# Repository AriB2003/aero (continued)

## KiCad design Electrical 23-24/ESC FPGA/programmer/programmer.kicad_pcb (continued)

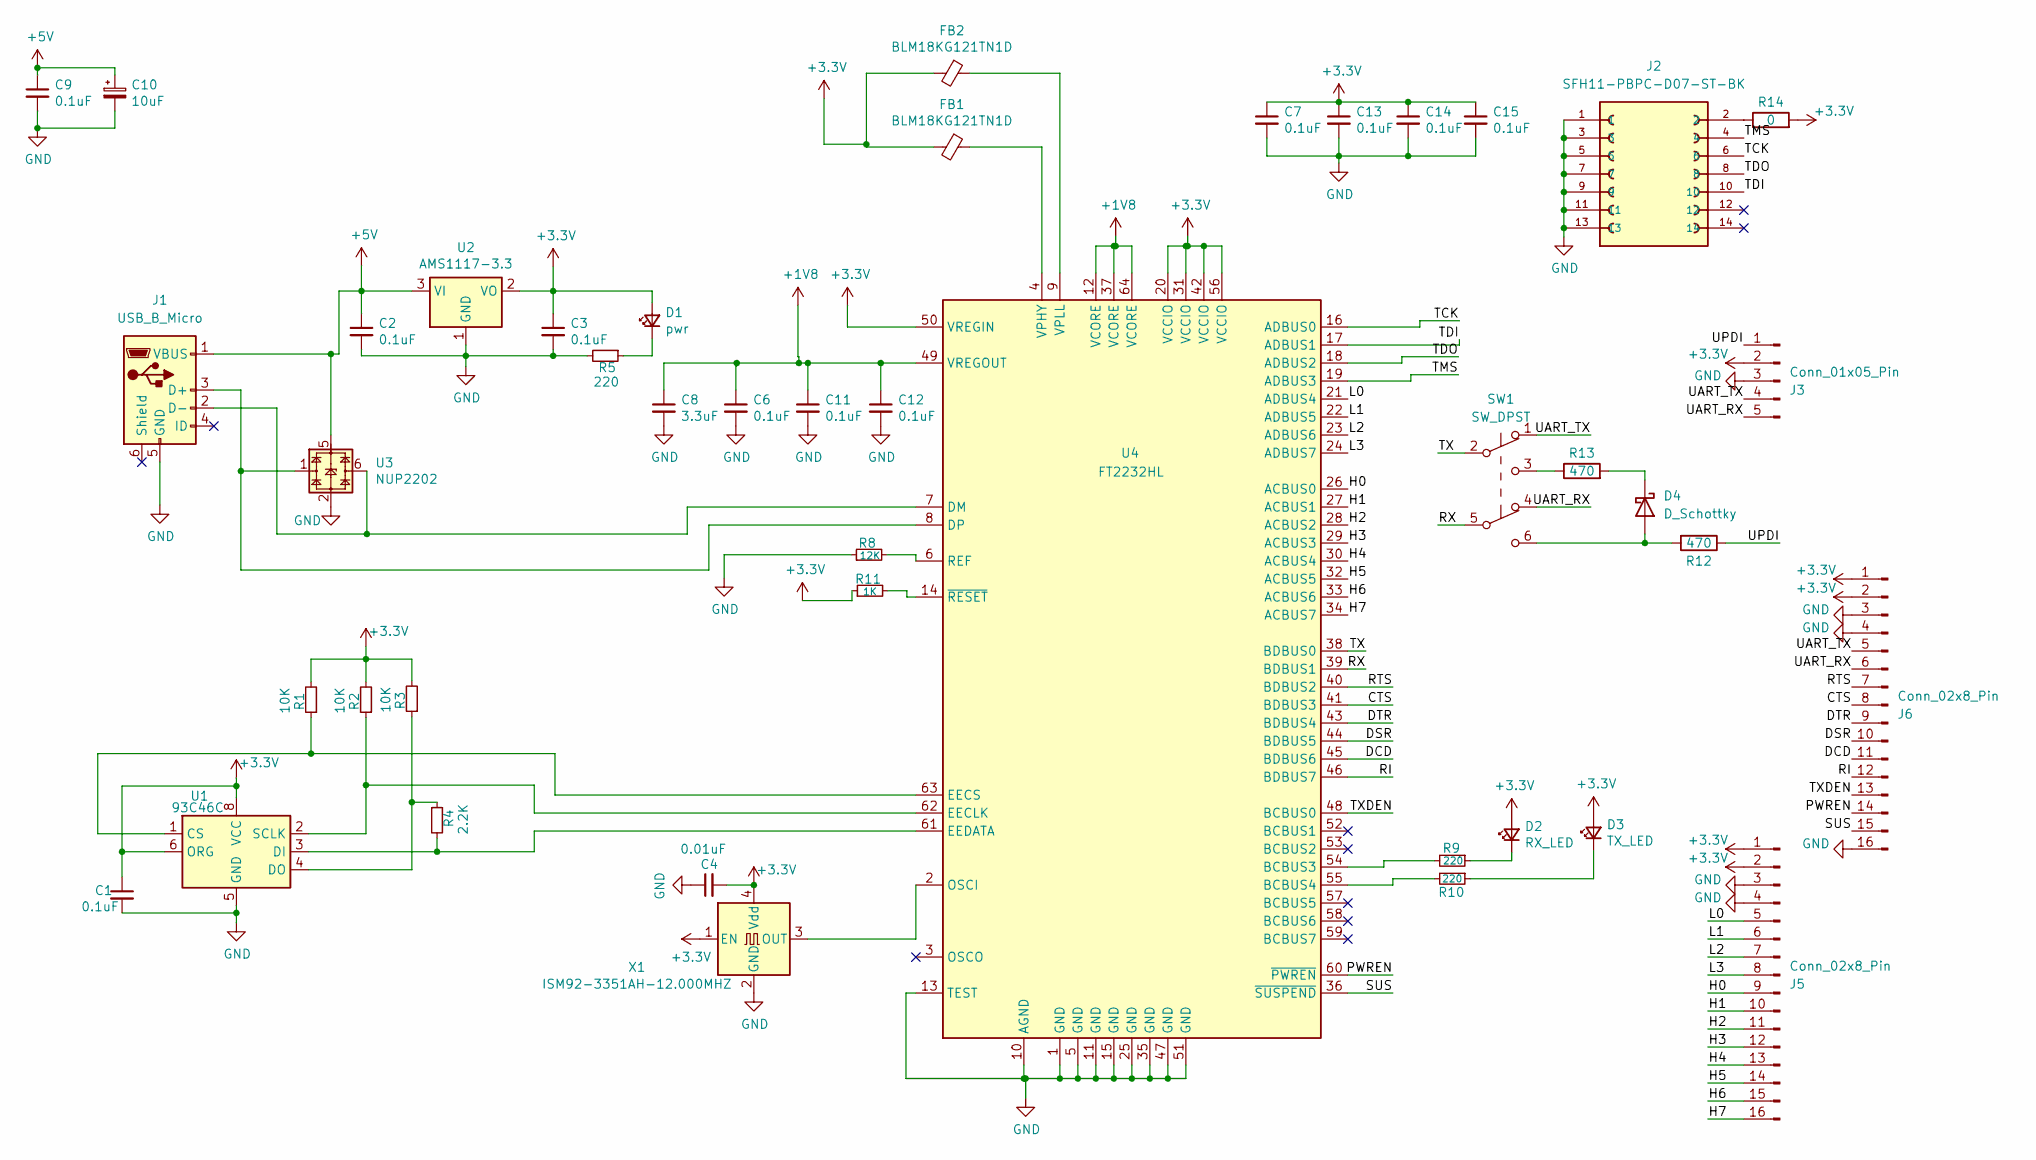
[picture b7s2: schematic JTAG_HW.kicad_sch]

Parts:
C1, C2, C3, C6, C7, C9, C11, C12, C13, C14, C15: 0.1uF; C_0603_1608Metric_Pad1.08x0.95mm_HandSolder
C4: 0.01uF; C_0603_1608Metric_Pad1.08x0.95mm_HandSolder
C8: 3.3uF; C_0603_1608Metric_Pad1.08x0.95mm_HandSolder
C10: 10uF; C_0603_1608Metric_Pad1.08x0.95mm_HandSolder
D1: pwr; LED_0603_1608Metric_Pad1.05x0.95mm_HandSolder
D2: RX_LED; LED_0603_1608Metric_Pad1.05x0.95mm_HandSolder
D3: TX_LED; LED_0603_1608Metric_Pad1.05x0.95mm_HandSolder
D4: D_Schottky; D_0603_1608Metric_Pad1.05x0.95mm_HandSolder
FB1, FB2: BLM18KG121TN1D; L_0603_1608Metric_Pad1.05x0.95mm_HandSolder
J1: USB_B_Micro; USB_Micro-B_Amphenol_10118193-0001LF_Horizontal
J2: SFH11-PBPC-D07-ST-BK; SULLINS_SFH11-PBPC-D07-ST-BK; PARTREV J
J3: Conn_01x05_Pin; PinSocket_1x05_P2.54mm_Horizontal
J5, J6: Conn_02x8_Pin; PinHeader_2x08_P2.54mm_Vertical
R1, R2, R3: 10K; R_0603_1608Metric_Pad0.98x0.95mm_HandSolder
R4: 2.2K; R_0603_1608Metric_Pad0.98x0.95mm_HandSolder
R5, R9, R10: 220; R_0603_1608Metric_Pad0.98x0.95mm_HandSolder
R8: 12K; R_0603_1608Metric_Pad0.98x0.95mm_HandSolder
R11: 1K; R_0603_1608Metric_Pad0.98x0.95mm_HandSolder
R12, R13: 470; R_0603_1608Metric_Pad0.98x0.95mm_HandSolder
R14: 0; R_0603_1608Metric_Pad0.98x0.95mm_HandSolder
SW1: SW_DPST; DPDT
U1: 93C46C; SOIC-8_3.9x4.9mm_P1.27mm
U2: AMS1117-3.3; SOT-223
U3: NUP2202; SOT-363_SC-70-6
U4: FT2232HL; LQFP-64_10x10mm_P0.5mm
X1: ISM92-3351AH-12.000MHZ; Oscillator_SMD_Abracon_ASE-4Pin_3.2x2.5mm_HandSoldering

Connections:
+1V8: C6.1, C8.1, C11.1, C12.1, U4.12 (VCORE), U4.37 (VCORE), U4.49 (VREGOUT), U4.64 (VCORE)
+3.3V: C1.1, C3.1, C4.2, C7.1, C13.1, C14.1, C15.1, D1.2 (A), D2.2 (A), D3.2 (A), FB1.2, FB2.2, J3.2, J5.1, J5.2, J6.1, J6.2, R1.2, R2.2, R3.2, R11.1, R14.2, U1.6 (ORG), U1.8 (VCC), U2.2 (VO), U4.20 (VCCIO), U4.31 (VCCIO), U4.42 (VCCIO), U4.50 (VREGIN), U4.56 (VCCIO), X1.1 (EN), X1.4 (Vdd)
+5V: C2.1, C9.1, C10.1, J1.1 (VBUS), U2.3 (VI), U3.5
/prog/CTS: J6.8, U4.41 (BDBUS3)
/prog/DCD: J6.11, U4.45 (BDBUS6)
/prog/DSR: J6.10, U4.44 (BDBUS5)
/prog/DTR: J6.9, U4.43 (BDBUS4)
/prog/H0: J5.9, U4.26 (ACBUS0)
/prog/H1: J5.10, U4.27 (ACBUS1)
/prog/H2: J5.11, U4.28 (ACBUS2)
/prog/H3: J5.12, U4.29 (ACBUS3)
/prog/H4: J5.13, U4.30 (ACBUS4)
/prog/H5: J5.14, U4.32 (ACBUS5)
/prog/H6: J5.15, U4.33 (ACBUS6)
/prog/H7: J5.16, U4.34 (ACBUS7)
/prog/L0: J5.5, U4.21 (ADBUS4)
/prog/L1: J5.6, U4.22 (ADBUS5)
/prog/L2: J5.7, U4.23 (ADBUS6)
/prog/L3: J5.8, U4.24 (ADBUS7)
/prog/PWREN: J6.14, U4.60 (~PWREN)
/prog/RI: J6.12, U4.46 (BDBUS7)
/prog/RTS: J6.7, U4.40 (BDBUS2)
/prog/RX: SW1.5 (B), U4.39 (BDBUS1)
/prog/SUS: J6.15, U4.36 (~SUSPEND)
/prog/TCK: J2.6, U4.16 (ADBUS0)
/prog/TDI: J2.10, U4.17 (ADBUS1)
/prog/TDO: J2.8, U4.18 (ADBUS2)
/prog/TMS: J2.4, U4.19 (ADBUS3)
/prog/TX: SW1.2 (B), U4.38 (BDBUS0)
/prog/TXDEN: J6.13, U4.48 (BCBUS0)
/prog/UART_RX: J3.5, J6.6, SW1.4 (A)
/prog/UART_TX: J3.4, J6.5, SW1.1 (A)
/prog/UPDI: J3.1, R12.1
GND: C1.2, C2.2, C3.2, C4.1, C6.2, C7.2, C8.2, C9.2, C10.2, C11.2, C12.2, C13.2, C14.2, C15.2, J1.5 (GND), J2.1, J2.3, J2.5, J2.7, J2.9, J2.11, J2.13, J3.3, J5.3, J5.4, J6.3, J6.4, J6.16, R5.2, R8.1, U1.5 (GND), U2.1 (GND), U3.2, U4.1 (GND), U4.5 (GND), U4.10 (AGND), U4.11 (GND), U4.13 (TEST), U4.15 (GND), U4.25 (GND), U4.35 (GND), U4.47 (GND), U4.51 (GND), X1.2 (GND)
unnamed: D1.1 (K), R5.1
unnamed: D2.1 (K), R9.1
unnamed: D3.1 (K), R10.1
unnamed: D4.2 (A), R12.2, SW1.6 (C)
unnamed: D4.1 (K), R13.2
unnamed: J1.3 (D+), U3.1, U4.8 (DP)
unnamed: J1.2 (D-), U3.6, U4.7 (DM)
unnamed: J2.2, R14.1
unnamed: R13.1, SW1.3 (C)
unnamed: R1.1, U1.1 (CS), U4.63 (EECS)
unnamed: R4.2, U1.3 (DI), U4.61 (EEDATA)
unnamed: R3.1, R4.1, U1.4 (DO)
unnamed: R2.1, U1.2 (SCLK), U4.62 (EECLK)
unnamed: R9.2, U4.54 (BCBUS3)
unnamed: R10.2, U4.55 (BCBUS4)
unnamed: U4.2 (OSCI), X1.3 (OUT)
unnamed: R8.2, U4.6 (REF)
unnamed: FB1.1, U4.4 (VPHY)
unnamed: FB2.1, U4.9 (VPLL)
unnamed: R11.2, U4.14 (~RESET)

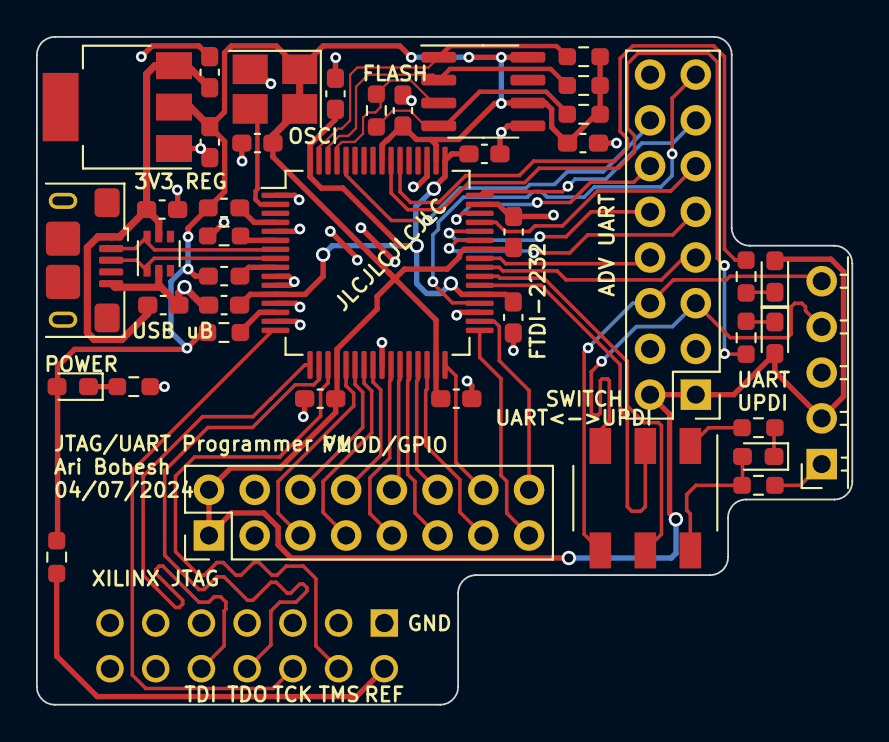
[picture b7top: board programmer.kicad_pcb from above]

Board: 2 copper layers, 45.3 x 37.1 mm, 43 parts (1 on the bottom side), 54 nets.

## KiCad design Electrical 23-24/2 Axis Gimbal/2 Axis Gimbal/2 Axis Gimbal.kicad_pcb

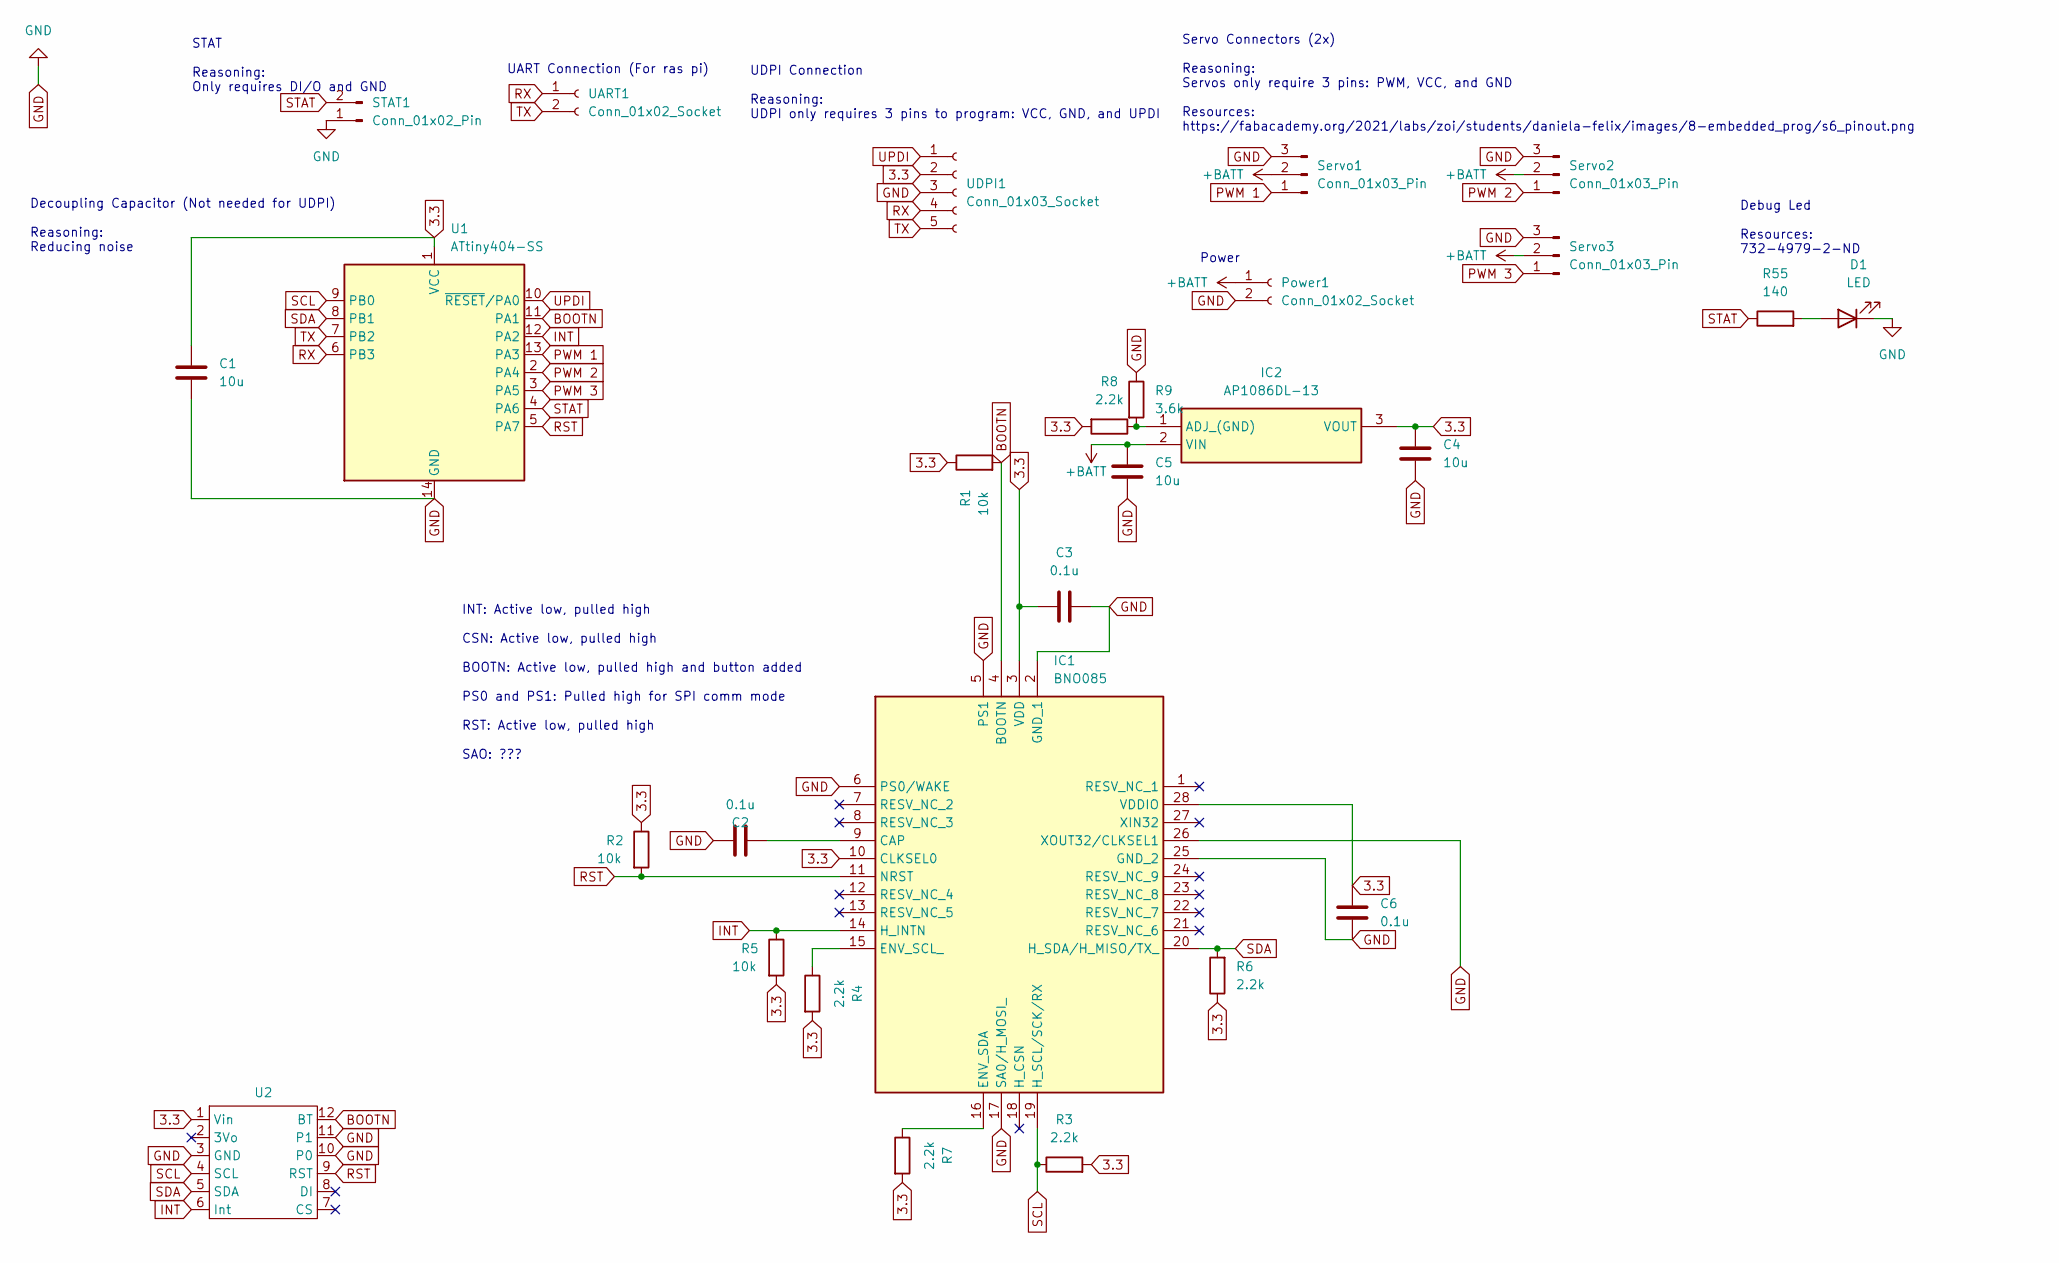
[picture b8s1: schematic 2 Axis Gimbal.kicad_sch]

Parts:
C1: 10u; C_0603_1608Metric_Pad1.08x0.95mm_HandSolder; MPN 1276-1052-1-ND
C2, C3, C6: 0.1u; C_0603_1608Metric_Pad1.08x0.95mm_HandSolder; MPN 478-3352-1-ND
C4, C5: 10u; C_0603_1608Metric_Pad1.08x0.95mm_HandSolder; MPN 445-1413-1-ND
D1: LED; LED_0603_1608Metric_Pad1.05x0.95mm_HandSolder
IC1: BNO085; Mouser Part Number 526-BNO085
IC2: AP1086DL-13; TO252-3L_1; Mouser Part Number 621-AP1086DL-13
Power1: Conn_01x02_Socket; JST_XH_B2B-XH-A_1x02_P2.50mm_Vertical
R1, R2, R5: 10k; R_0603_1608Metric_Pad0.98x0.95mm_HandSolder
R3, R4, R6, R7, R8: 2.2k; R_0603_1608Metric_Pad0.98x0.95mm_HandSolder
R9: 3.6k; R_0603_1608Metric_Pad0.98x0.95mm_HandSolder
R55: 140; R_0603_1608Metric_Pad0.98x0.95mm_HandSolder
STAT1: Conn_01x02_Pin; JST_XH_B2B-XH-A_1x02_P2.50mm_Vertical
Servo1, Servo2, Servo3: Conn_01x03_Pin; JST_XH_B3B-XH-A_1x03_P2.50mm_Vertical
U1: ATtiny404-SS; SOIC-14_3.9x8.7mm_P1.27mm
U2: breakout
UART1: Conn_01x02_Socket; JST_XH_B2B-XH-A_1x02_P2.50mm_Vertical
UDPI1: Conn_01x03_Socket; PinSocket_1x05_P2.54mm_Vertical

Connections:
3.3: C1.1, C3.1, C4.1, C6.1, IC1.3 (VDD), IC1.10 (CLKSEL0), IC1.28 (VDDIO), IC2.3 (VOUT), R1.1, R2.1, R3.2, R4.2, R5.2, R6.1, R7.2, R8.2, U1.1 (VCC), U2.1 (Vin), UDPI1.2
+BATT: C5.1, IC2.2 (VIN), Power1.1, Servo1.2, Servo2.2, Servo3.2
BOOTN: IC1.4 (BOOTN), R1.2, U1.11 (PA1), U2.12 (BT)
GND: C1.2, C2.1, C3.2, C4.2, C5.2, C6.2, D1.1 (K), IC1.2 (GND_1), IC1.5 (PS1), IC1.6 (PS0/WAKE), IC1.17 (SA0/H_MOSI_), IC1.25 (GND_2), IC1.26 (XOUT32/CLKSEL1), Power1.2, R9.1, STAT1.1, Servo1.3, Servo2.3, Servo3.3, U1.14 (GND), U2.3 (GND), U2.10 (P0), U2.11 (P1), UDPI1.3
INT: IC1.14 (H_INTN), R5.1, U1.12 (PA2), U2.6 (Int)
unnamed: D1.2 (A), R55.2
unnamed: C2.2, IC1.9 (CAP)
unnamed: IC1.15 (ENV_SCL_), R4.1
unnamed: IC1.16 (ENV_SDA), R7.1
unnamed: IC2.1 (ADJ_(GND)), R8.1, R9.2
PWM 1: Servo1.1, U1.13 (PA3)
PWM 2: Servo2.1, U1.2 (PA4)
PWM 3: Servo3.1, U1.3 (PA5)
RST: IC1.11 (NRST), R2.2, U1.5 (PA7), U2.9 (RST)
RX: U1.6 (PB3), UART1.1, UDPI1.4
SCL: IC1.19 (H_SCL/SCK/RX), R3.1, U1.9 (PB0), U2.4 (SCL)
SDA: IC1.20 (H_SDA/H_MISO/TX_), R6.2, U1.8 (PB1), U2.5 (SDA)
STAT: R55.1, STAT1.2, U1.4 (PA6)
TX: U1.7 (PB2), UART1.2, UDPI1.5
UPDI: U1.10 (~RESET/PA0), UDPI1.1

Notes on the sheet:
INT: Active low, pulled high CSN: Active low, pulled high BOOTN: Active low, pulled high and button added PS0 and PS1: Pulled high for SPI comm mode RST: Active low, pulled high SAO: ???
STAT Reasoning: Only requires DI/O and GND
UDPI Connection Reasoning: UDPI only requires 3 pins to program: VCC, GND, and UPDI
UART Connection (For ras pi)
Servo Connectors (2x) Reasoning: Servos only require 3 pins: PWM, VCC, and GND Resources: https://fabacademy.org/2021/labs/zoi/students/daniela-felix/images/8-embedded_prog/s6_pinout.png
Decoupling Capacitor (Not needed for UDPI) Reasoning: Reducing noise
Power
Debug Led Resources: 732-4979-2-ND

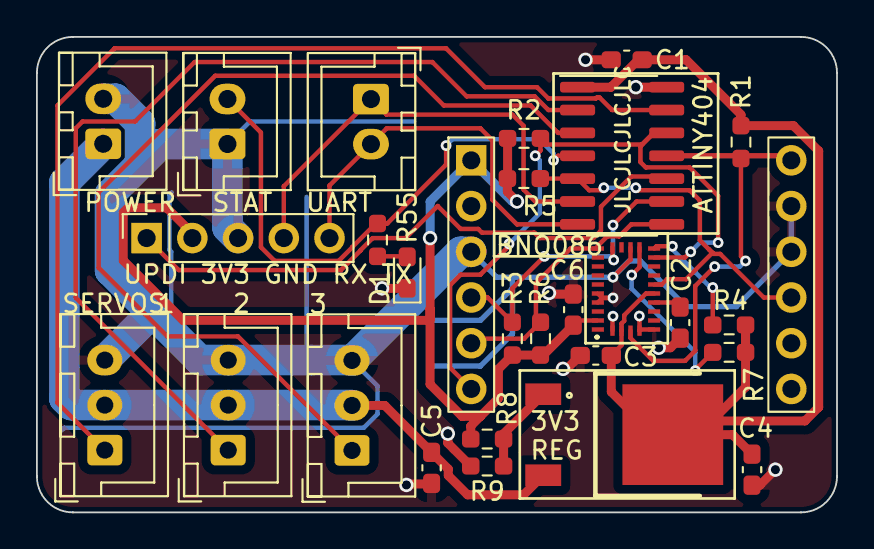
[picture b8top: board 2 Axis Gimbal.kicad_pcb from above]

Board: 2 copper layers, 44.5 x 26.4 mm, 28 parts (0 on the bottom side), 20 nets.

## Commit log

2024-02-28 Push PMB
2024-02-28 PDB_parts
2024-02-28 Finish schematic
2024-02-28 Add all footprints
2024-02-28 Started layout
2024-03-06 Finish PMB
2024-03-09 Added Project
2024-03-09 Fix some gimbal problems
2024-03-12 Added I2C
2024-03-12 Create 1
2024-03-12 Adding PDB Kicad Files
2024-03-12 Finished Final Schematic
2024-03-16 Final PMB
2024-03-22 Push start of FPGA file structure
2024-03-22 Finish programming interface with FPGA
2024-03-22 Updates to the PDB Design
    Pushed Some Buck Converters to the back
    Added more connectors (for RasPi, Bullet, etc.)
2024-03-23 Add programmer
2024-03-24 Added Footprints
2024-03-25 Starteddddd
2024-03-26 idk but something
2024-03-26 Adding Power Protection File
2024-03-29 Update 2 Axis Gimbal.kicad_pcb
    Finished PCB
2024-03-29 Final PDB (missing Aero Logo)
2024-04-02 DR Feedback
2024-04-02 Reformatted PCB
2024-04-02 Fix gimbal schematic
2024-04-02 Final Board
2024-04-03 Finished Gimbal Board
2024-04-06 Finalize PDB board
2024-04-06 Adding new parts
2024-04-06 Barely Started on Layout
2024-04-07 Finish programmer schematic w/ Digi
2024-04-07 Layout almost done, need to try routing
2024-04-07 Finished the core, connecting ports
2024-04-07 Finished length matched traces
2024-04-07 Finished routing, need to add planes
2024-04-07 Finished layout, need to DRC
2024-04-07 Finished board
2024-04-07 Add JLC Serial # Location to All
2024-04-17 Changing JST EH to JST XH connector for Gimbal
2024-04-17 Fix a MAJOR issue that ANTHONY caused
2024-04-17 Changed USB micro to USB A
2024-04-17 Finish programmer BOM
2024-04-19 Begin JLC exports
2024-04-20 Final board exports
2024-04-26 Add fpga stuff and stencils
2024-04-26 Gimbal stencil
2024-04-27 Stencil for PMB and programmer
2024-04-27 Added SVG files
2024-04-27 Made stencils
2024-04-27 added svg
2024-04-28 Working on FPGA board
2024-04-28 Add level shifters
2024-04-28 Finished FPGA board schematic
2024-04-30 Made BOM, need to modify footprints
2024-08-23 Finish groupings on FPGA PCB
2024-08-23 Finished hard signal routing, need PMOD and Power
2024-08-24 Finish PCB layout, need to DRC
2024-08-24 Turn XT60
2024-09-06 Add schematic for servo tester
2024-09-08 Add silkscreen to FPGA
2024-09-09 Add servo tester layout
2024-09-10 Finish servo tester silk
2024-09-17 Updated folders and schematic for onboarding
2024-09-18 Add symbol library for onboarding.
2024-09-18 Started servo tester schematic
2024-09-21 added some led wires
2024-09-26 Current iteration
    No idea what I am doing
2024-10-01 Update Tester.kicad_sch
    Progress has been made.
2024-10-01 The board is almost done
    Mostly done except that I'm not sure about the filter and I need to know whether to connect the LCD as I2C or otherwise
2024-10-02 Board components ready except encoder
    The board footprints are now uploaded to a new folder and the pcb layout is ready to be made.
2024-10-02 did shit
2024-10-02 more shit
2024-10-14 Add some servo tester enclosure and code
2024-11-08 Add groundstation
2024-11-08 Create imageReciever
2024-11-08 Created imageSender.py
2024-11-09 Test_bat
2024-11-09 test_bat1
2024-11-20 added image sender and reciever code, these are the ip address that works with radiogit status
2024-12-02 setting up the ros2 files
2024-12-09 groundstation
2024-12-09 requirements
2024-12-11 working sim[ple published and subscriber
2024-12-11 trying to fix git
2024-12-11 restored changes on own branch
2024-12-14 hello ari
2025-01-06 Add files via upload
    Pulls quaternion rotation vector values from the imu.
2025-01-16 editting alg
2025-01-25 I did some shit, I started a new version that only uses the 3 nearest points
2025-01-25 closing rate
2025-01-25 delete
2025-01-26 added mavlink and simulation to test it
2025-01-29 working orbit in sim
2025-01-29 added requirements.txt
2025-01-29 working rejection vector (w/ Ari's help)
2025-01-29 new requirements.txt plz work
2025-01-31 Got the model working - it now saves info to detections.csv: class name, time, and bounding box values
2025-02-04 new code for testing pixhawk talk tuah, in progress
2025-02-11 First commit to aero repo. Currently translating c++ code to python code for OpenCV motion deblur.
2025-02-11 Working on making psf
2025-02-11 Made string path of waypoints
2025-02-12 successfully created and displayed point spread function
2025-02-12 cleaner point spread function code
2025-02-14 clean up and document point spread function
2025-02-17 Start working on full code
2025-02-17 Working on state transitions
2025-02-17 Full servo tester code works
2025-02-17 Minor initialization bug
2025-02-17 Final state issue resolved
2025-02-18 Add fft quadrant shift function
2025-02-25 Started working on edgetaper function
2025-03-04 Electromagnetic dropping mechanism first draft. Labels and indicators yet to be included.
2025-03-04 added edgetaper function, need to test and review it
2025-03-05 Rough PCB layout with completed schematic.
2025-03-06 Adding datasheet for USB-A connector
2025-03-06 Dropping Mechanism BOM
2025-03-06 Delete AERO_BOM.xlsx
    Missing Red LED
2025-03-11 edgetaper may run properly
2025-03-14 Updates pcb with 0608metric
2025-03-24 integrated and set up telemetry in ros2, haven't fully tested because i dont wanna set up rasbpi but like it should work just trust me bro
2025-03-24 got telemetry and waypoints working with hardcoded values, now I need to test with whole rasbpi and real values, also need to get this to somehow takeoff and land and fly a freaking plane but thats a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
2025-03-25 made but didn't test the last 2 calculation methods
2025-03-28 Finalized dropping mechanism PCB.
2025-03-28 Finished base code, debugging issues with cv channel merge
2025-03-31 Logo added and silkscreen improved
2025-04-01 Full code runs but does not properly deblur
2025-04-03 Final final dropping mechanism pcb.
2025-04-04 fixed psf, need to fix edgetaper
2025-04-08 edge_taper works, need to handle dtype issues in filter2dfreq
2025-04-11 image correctly processed when LEN is 1
2025-04-15 debugging disconnect between matlab and python opencv fftshift
2025-04-18 fixed fftshift naming, still debugging filter creation
2025-04-21 Prints for the servo tester
2025-04-21 Add newest version of path planning
2025-04-22 more debugging
2025-04-22 Refactor path planning algorithm code
2025-04-27 tested the cpp code, the implementations are the same
2025-04-28 added images to gitignore
2025-04-29 testing cpp code
2025-05-02 slight_word_blur deblurred with len 175, theta 5, snr 15
2025-09-16 PCBDrone Schematic, In Progress
2025-09-20 Schematic tentatively done
2025-09-30 Symbol and Footprint libraries cleaned up, footprints assigned to every symbol, and placed in PCB editor. Starting work on footprint.
2025-10-21 Everything done except logo and name
2025-10-23 Finished PCB
